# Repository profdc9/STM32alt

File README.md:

This is a Bluepill-compatible devboard for the STM32F103C8T6 microcontroller.
It uses all through-hole parts except for the STM32F103C8T6/STM32F103CBT6 microcontroller
and is intended to be an alternative to the Bluepill that is easier to assemble
should the Bluepill not be available or suitable.  It is somewhat optimized to be
RFI resistant given it is a two-layer board
This material is copyrighted by Daniel Marks (KW4TI) and licensed under
the Creative Commons License CC-BY-SA 4.0.  Software is copyrighted using the zlib
open-source license.

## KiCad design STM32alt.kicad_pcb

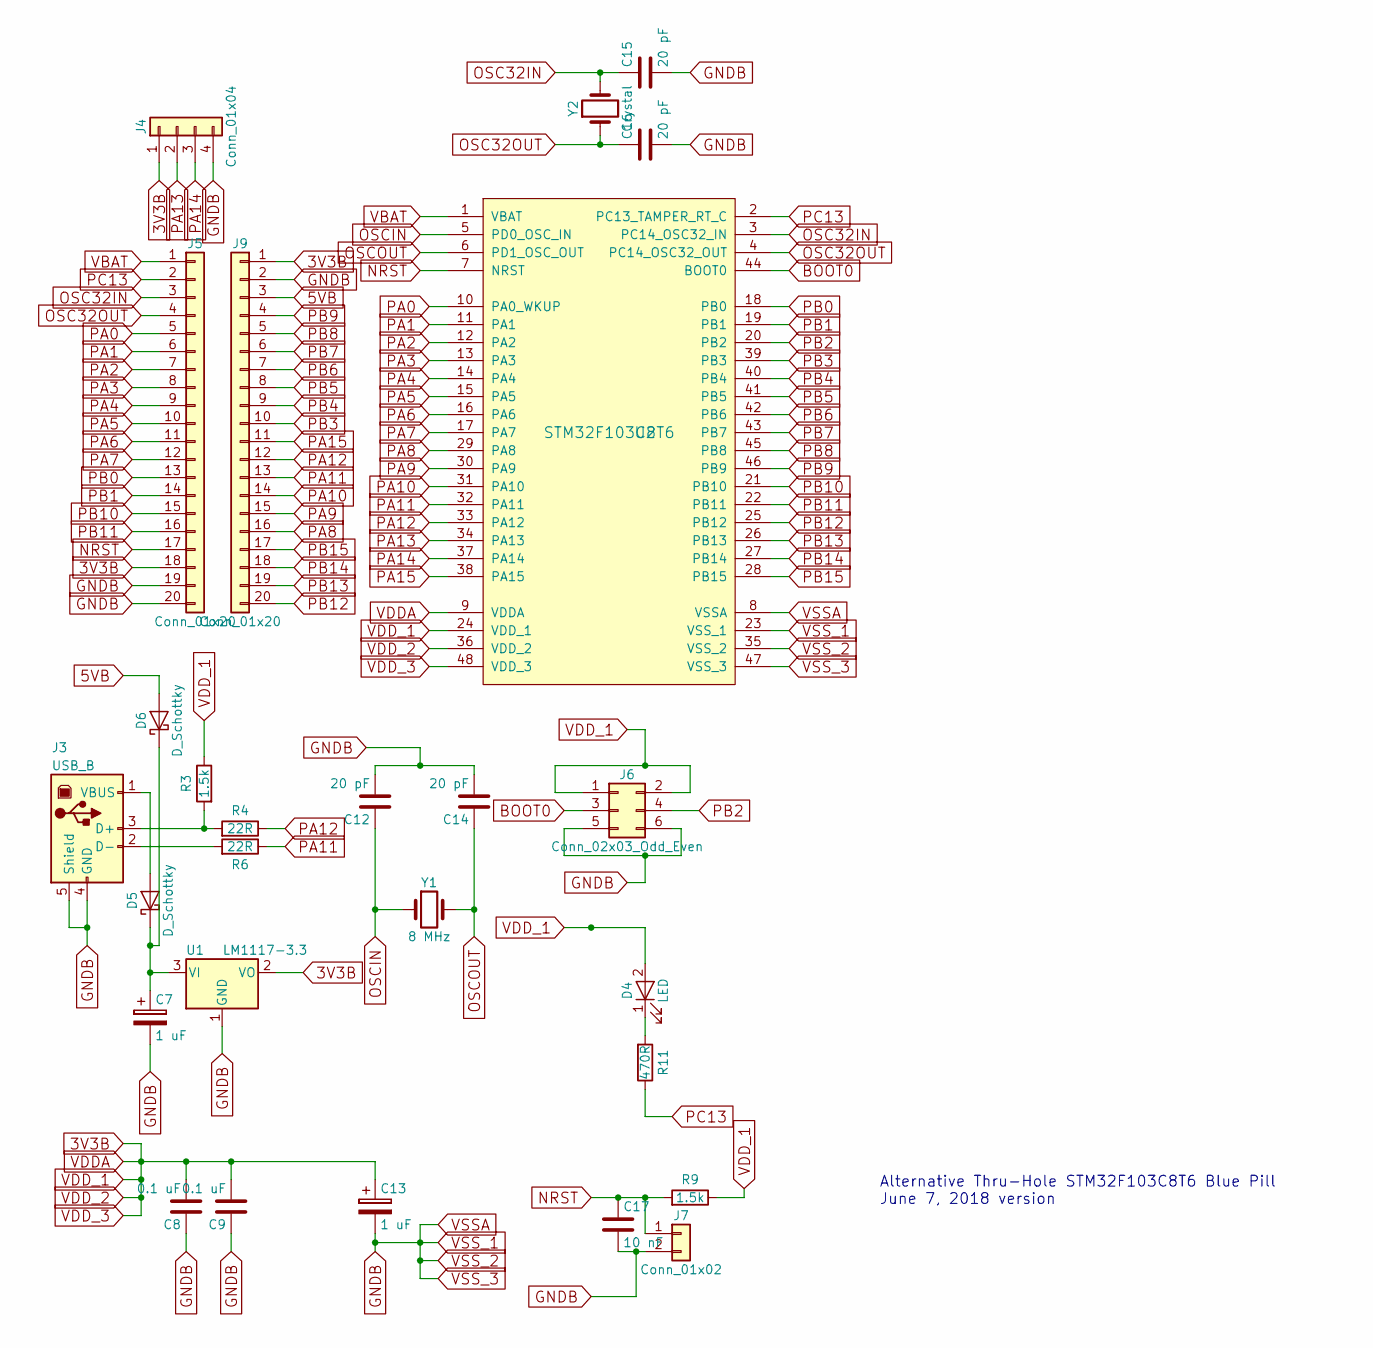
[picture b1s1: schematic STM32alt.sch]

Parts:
C7, C13: 1 uF; CP_Radial_D5.0mm_P2.50mm
C8, C9: 0.1 uF; C_Disc_D5.0mm_W2.5mm_P2.50mm
C12, C14, C15, C16: 20 pF; C_Disc_D5.0mm_W2.5mm_P2.50mm
C17: 10 nF; C_Disc_D5.0mm_W2.5mm_P2.50mm
D4: LED; LED_D3.0mm
D5, D6: D_Schottky; D_DO-41_SOD81_P7.62mm_Horizontal
J3: USB_B
J4: Conn_01x04; Pin_Header_Straight_1x04_Pitch2.54mm
J5, J9: Conn_01x20; Pin_Header_Straight_1x20_Pitch2.54mm
J6: Conn_02x03_Odd_Even; Pin_Header_Straight_2x03_Pitch2.54mm
J7: Conn_01x02; SW_PUSH_6mm
R3, R9: 1.5k; R_Axial_DIN0207_L6.3mm_D2.5mm_P7.62mm_Horizontal
R4, R6: 22R; R_Axial_DIN0207_L6.3mm_D2.5mm_P7.62mm_Horizontal
R11: 470R; R_Axial_DIN0207_L6.3mm_D2.5mm_P7.62mm_Horizontal
U1: LM1117-3.3; TO-220-3_Vertical
U2: STM32F103C8T6; LQFP-48_7x7mm_Pitch0.5mm
Y1: 8 MHz; Crystal_HC49-U_Vertical
Y2: Crystal; Crystal_Round_d2.0mm_Vertical

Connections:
3V3B: C8.2, C9.2, C13.1, D4.2 (A), J4.1, J5.18, J6.1, J6.2, J9.1, R3.1, R9.1, U1.2 (VO), U2.9 (VDDA), U2.24 (VDD_1), U2.36 (VDD_2), U2.48 (VDD_3)
5VB: D6.2 (A), J9.3
BOOT0: J6.3, U2.44 (BOOT0)
GNDB: C7.2, C8.1, C9.1, C12.2, C13.2, C14.2, C15.2, C16.2, C17.2, J3.4 (GND), J3.5 (Shield), J4.4, J5.19, J5.20, J6.5, J6.6, J7.2, J9.2, U1.1 (GND), U2.8 (VSSA), U2.23 (VSS_1), U2.35 (VSS_2), U2.47 (VSS_3)
NRST: C17.1, J5.17, J7.1, R9.2, U2.7 (NRST)
unnamed: C7.1, D5.1 (K), D6.1 (K), U1.3 (VI)
unnamed: D4.1 (K), R11.2
unnamed: D5.2 (A), J3.1 (VBUS)
unnamed: J3.2 (D-), R6.2
unnamed: J3.3 (D+), R3.2, R4.2
OSC32IN: C15.1, J5.3, U2.3 (PC14_OSC32_IN), Y2.2
OSC32OUT: C16.1, J5.4, U2.4 (PC14_OSC32_OUT), Y2.1
OSCIN: C12.1, U2.5 (PD0_OSC_IN), Y1.1
OSCOUT: C14.1, U2.6 (PD1_OSC_OUT), Y1.2
PA0: J5.5, U2.10 (PA0_WKUP)
PA1: J5.6, U2.11 (PA1)
PA2: J5.7, U2.12 (PA2)
PA3: J5.8, U2.13 (PA3)
PA4: J5.9, U2.14 (PA4)
PA5: J5.10, U2.15 (PA5)
PA6: J5.11, U2.16 (PA6)
PA7: J5.12, U2.17 (PA7)
PA8: J9.16, U2.29 (PA8)
PA9: J9.15, U2.30 (PA9)
PA10: J9.14, U2.31 (PA10)
PA11: J9.13, R6.1, U2.32 (PA11)
PA12: J9.12, R4.1, U2.33 (PA12)
PA13: J4.2, U2.34 (PA13)
PA14: J4.3, U2.37 (PA14)
PA15: J9.11, U2.38 (PA15)
PB0: J5.13, U2.18 (PB0)
PB1: J5.14, U2.19 (PB1)
PB2: J6.4, U2.20 (PB2)
PB3: J9.10, U2.39 (PB3)
PB4: J9.9, U2.40 (PB4)
PB5: J9.8, U2.41 (PB5)
PB6: J9.7, U2.42 (PB6)
PB7: J9.6, U2.43 (PB7)
PB8: J9.5, U2.45 (PB8)
PB9: J9.4, U2.46 (PB9)
PB10: J5.15, U2.21 (PB10)
PB11: J5.16, U2.22 (PB11)
PB12: J9.20, U2.25 (PB12)
PB13: J9.19, U2.26 (PB13)
PB14: J9.18, U2.27 (PB14)
PB15: J9.17, U2.28 (PB15)
PC13: J5.2, R11.1, U2.2 (PC13_TAMPER_RT_C)
VBAT: J5.1, U2.1 (VBAT)

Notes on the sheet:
Alternative Thru-Hole STM32F103C8T6 Blue Pill June 7, 2018 version

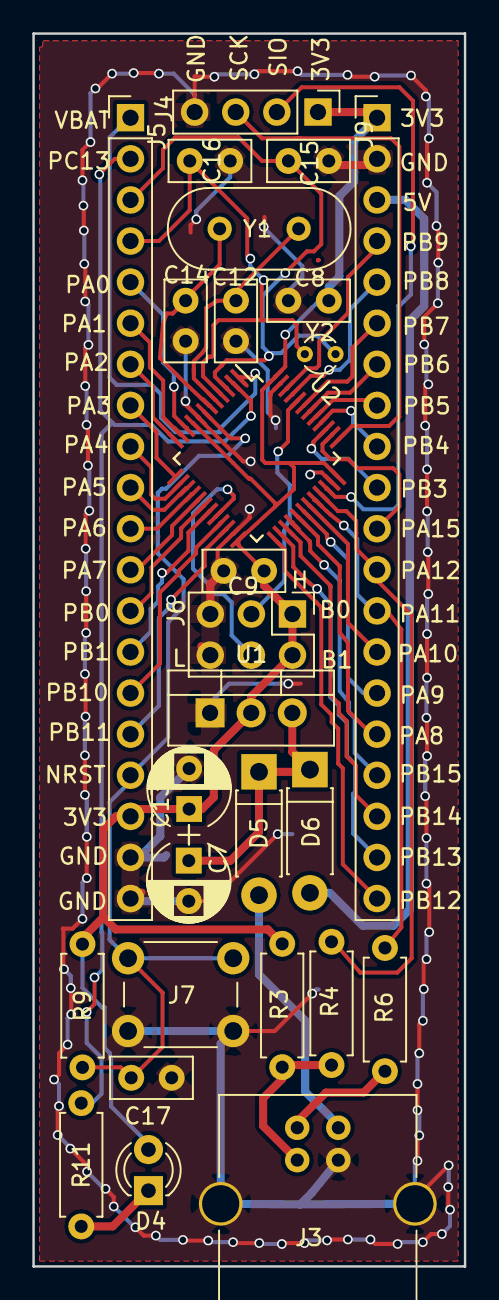
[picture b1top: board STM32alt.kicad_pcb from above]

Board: 2 copper layers, 26.7 x 76.2 mm, 27 parts (0 on the bottom side), 48 nets.

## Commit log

2018-10-08 Second Commit
2019-10-16 Moved center chip, flipped SWD connector, added ground ring
